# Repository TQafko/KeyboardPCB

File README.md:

# KeyboardPCB
The project aimed to create a Human Interface Device (HID) using an Arduino microcontroller with the Atmega32U4 chip. The keyboard was to be used for additional keys to a laptop to allow the user easier access to certain characters; adding a numeric numpad. As computers use drivers to understand what external USB devices are trying to communicate, this device was designed and programmed to send ASCI characters through the USB2.0 protocol.

## Comarpison of Atmega328 vs Atmega32U4
Due to HID devices requiring a USB interface a microcontroller using the Atmega 32U4 chip was selected. By comparing the two functional block diagrams below of the two chips, the Atmega 32U4 contains the USB2.0 block that allows the computer to directly communicate via USB to the chip and therefore not requiring a USB-to-Serial converter on board.  

## 3D Model

## Schematics

## Layout

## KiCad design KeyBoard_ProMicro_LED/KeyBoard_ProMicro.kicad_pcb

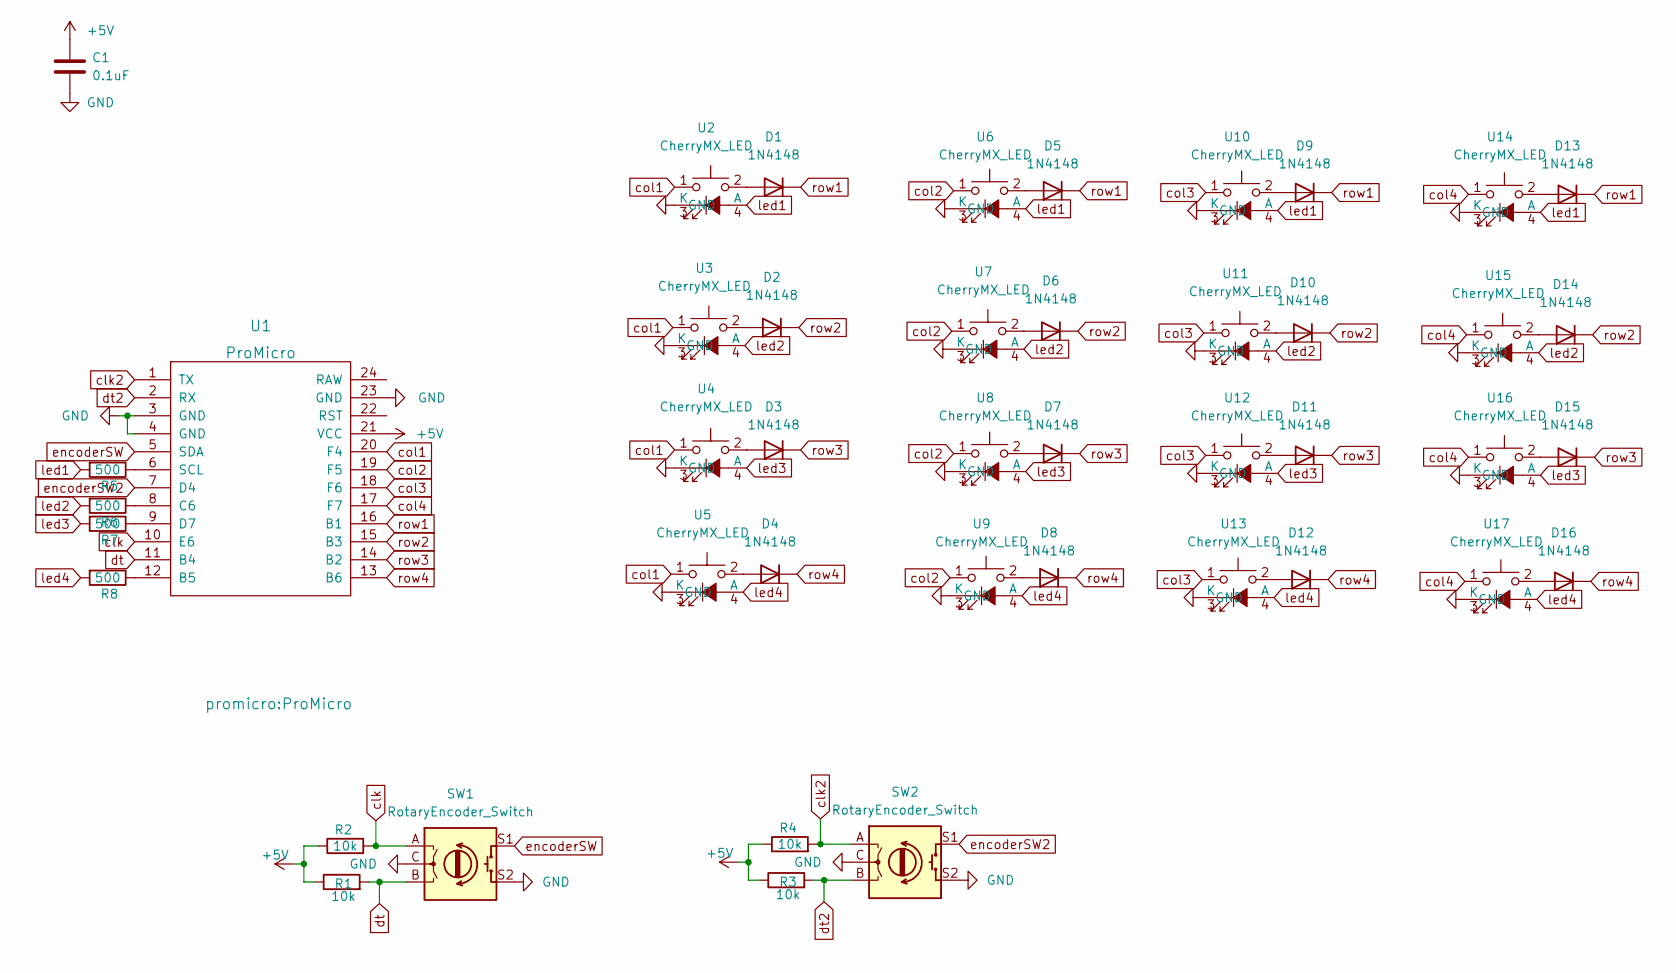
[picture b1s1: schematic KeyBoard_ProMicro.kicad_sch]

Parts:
C1: 0.1uF; C_1206_3216Metric
D1, D2, D3, D4, D5, D6, D7, D8, D9, D10, D11, D12, D13, D14, D15, D16: 1N4148; D_DO-35_SOD27_P7.62mm_Horizontal
R1, R2, R3, R4: 10k; R_Axial_DIN0207_L6.3mm_D2.5mm_P10.16mm_Horizontal
R5, R6, R7, R8: 500; R_Axial_DIN0207_L6.3mm_D2.5mm_P10.16mm_Horizontal
SW1, SW2: RotaryEncoder_Switch; RotaryEncoder_Alps_EC12E-Switch_Vertical_H20mm
U1: ProMicro
U2, U3, U4, U5, U6, U7, U8, U9, U10, U11, U12, U13, U14, U15, U16, U17: CherryMX_LED; CherryMX_1.00u_PCB_LED

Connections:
+5V: C1.1, R1.1, R2.1, R3.1, R4.1, U1.21 (VCC)
GND: C1.2, SW1.C, SW1.S2, SW2.C, SW2.S2, U1.3 (GND), U1.4 (GND), U1.23 (GND), U2.3 (K), U3.3 (K), U4.3 (K), U5.3 (K), U6.3 (K), U7.3 (K), U8.3 (K), U9.3 (K), U10.3 (K), U11.3 (K), U12.3 (K), U13.3 (K), U14.3 (K), U15.3 (K), U16.3 (K), U17.3 (K)
unnamed: D1.2 (A), U2.2
unnamed: D2.2 (A), U3.2
unnamed: D3.2 (A), U4.2
unnamed: D4.2 (A), U5.2
unnamed: D5.2 (A), U6.2
unnamed: D6.2 (A), U7.2
unnamed: D7.2 (A), U8.2
unnamed: D8.2 (A), U9.2
unnamed: D9.2 (A), U10.2
unnamed: D10.2 (A), U11.2
unnamed: D11.2 (A), U12.2
unnamed: D12.2 (A), U13.2
unnamed: D13.2 (A), U14.2
unnamed: D14.2 (A), U15.2
unnamed: D15.2 (A), U16.2
unnamed: D16.2 (A), U17.2
unnamed: R5.1, U1.6 (SCL)
unnamed: R6.1, U1.8 (C6)
unnamed: R7.1, U1.9 (D7)
unnamed: R8.1, U1.12 (B5)
clk: R2.2, SW1.A, U1.10 (E6)
clk2: R4.2, SW2.A, U1.1 (TX)
col1: U1.20 (F4), U2.1, U3.1, U4.1, U5.1
col2: U1.19 (F5), U6.1, U7.1, U8.1, U9.1
col3: U1.18 (F6), U10.1, U11.1, U12.1, U13.1
col4: U1.17 (F7), U14.1, U15.1, U16.1, U17.1
dt: R1.2, SW1.B, U1.11 (B4)
dt2: R3.2, SW2.B, U1.2 (RX)
encoderSW: SW1.S1, U1.5 (SDA)
encoderSW2: SW2.S1, U1.7 (D4)
led1: R5.2, U2.4 (A), U6.4 (A), U10.4 (A), U14.4 (A)
led2: R6.2, U3.4 (A), U7.4 (A), U11.4 (A), U15.4 (A)
led3: R7.2, U4.4 (A), U8.4 (A), U12.4 (A), U16.4 (A)
led4: R8.2, U5.4 (A), U9.4 (A), U13.4 (A), U17.4 (A)
row1: D1.1 (K), D5.1 (K), D9.1 (K), D13.1 (K), U1.16 (B1)
row2: D2.1 (K), D6.1 (K), D10.1 (K), D14.1 (K), U1.15 (B3)
row3: D3.1 (K), D7.1 (K), D11.1 (K), D15.1 (K), U1.14 (B2)
row4: D4.1 (K), D8.1 (K), D12.1 (K), D16.1 (K), U1.13 (B6)

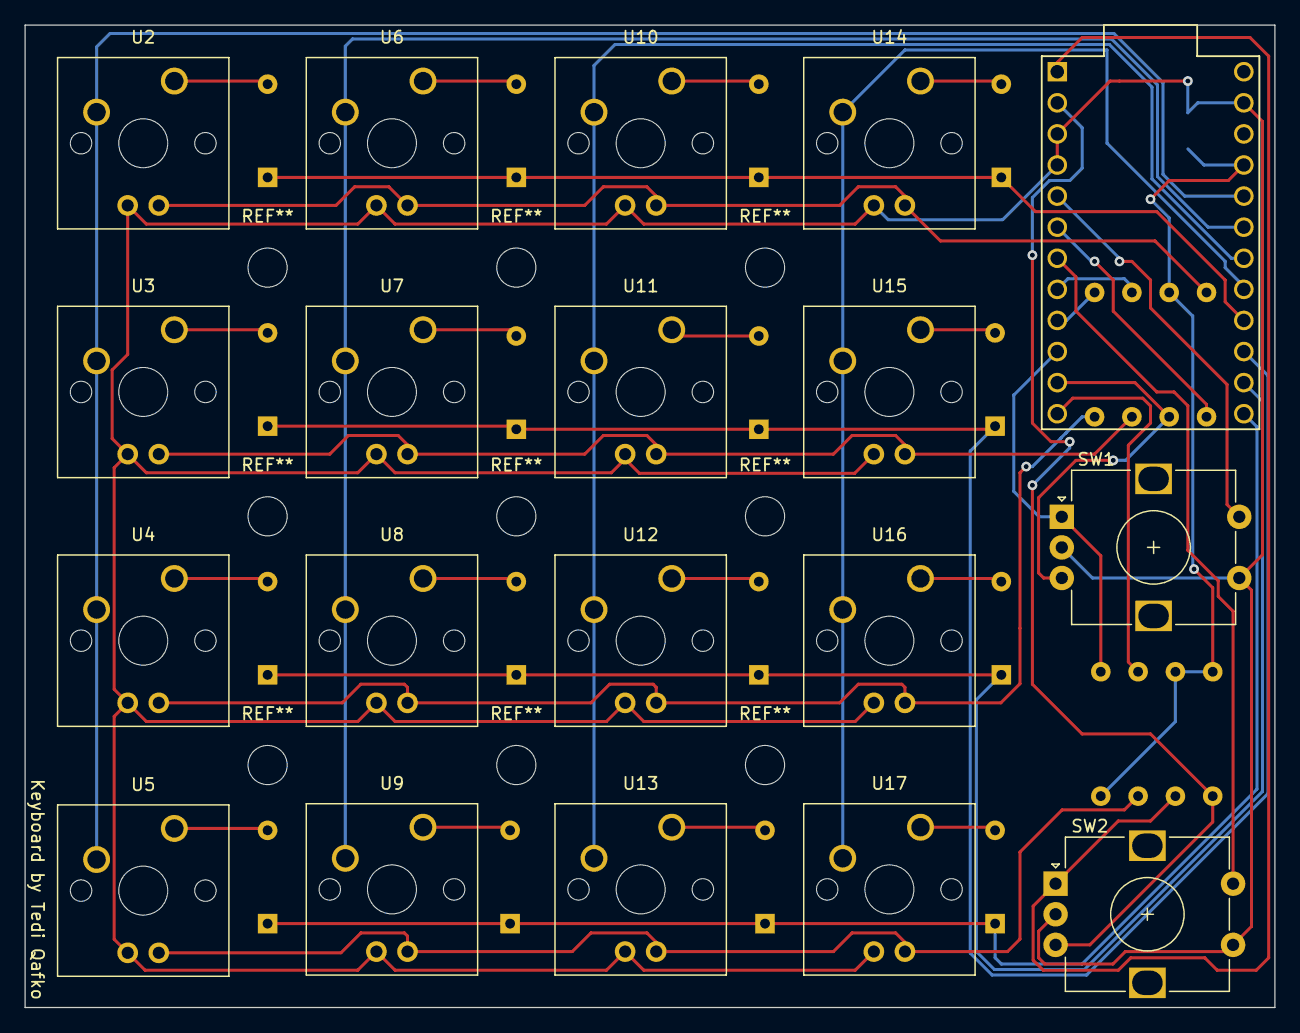
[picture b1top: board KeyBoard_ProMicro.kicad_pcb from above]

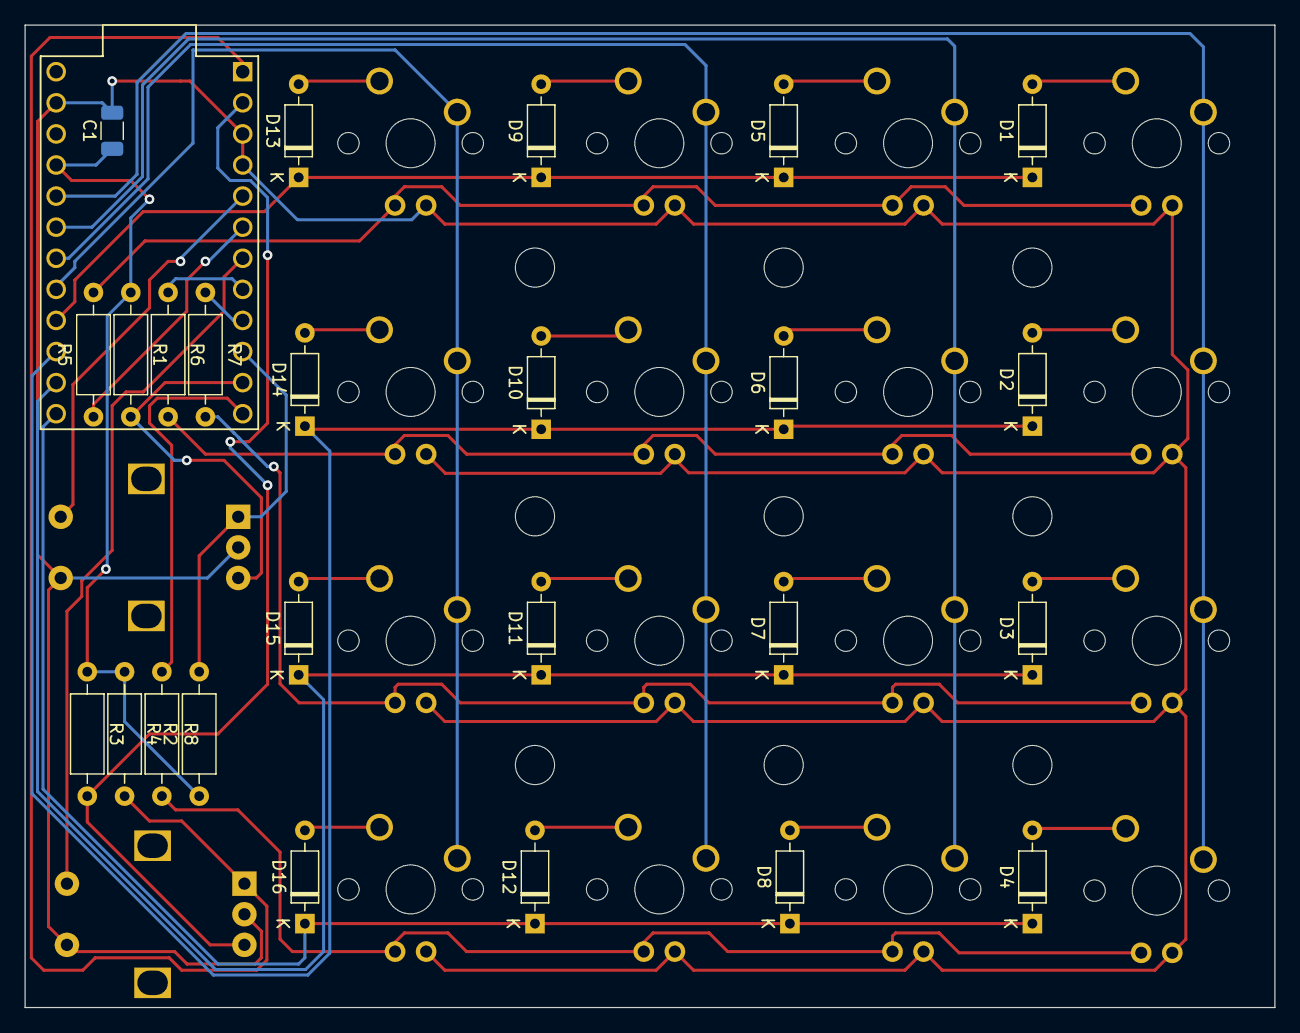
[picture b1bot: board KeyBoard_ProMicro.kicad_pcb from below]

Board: 2 copper layers, 102.1 x 80.3 mm, 44 parts (25 on the bottom side), 40 nets.
